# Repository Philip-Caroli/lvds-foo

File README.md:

# lvds-foo
Testing out some LVDS stuff.
Currently only playing around.

## in progress
 * LVDS shield for raspberry (zero) using the DPI interface

## used hardware
 * DPI -> LVDS Converter THC63LVD823B http://www.cel.com/pdf/datasheets/THC63LVD823B.pdf
 * Cable FIX-30P-D6
 * Display HSD150PX17 https://www.touchandscreen.de/mediafiles/Datasheets/HANNSTAR/HSD150PX17-A05.pdf
 
 ## Ressources
  * FIX-30P-D6 and FIX-30P-S8 difference and pinout

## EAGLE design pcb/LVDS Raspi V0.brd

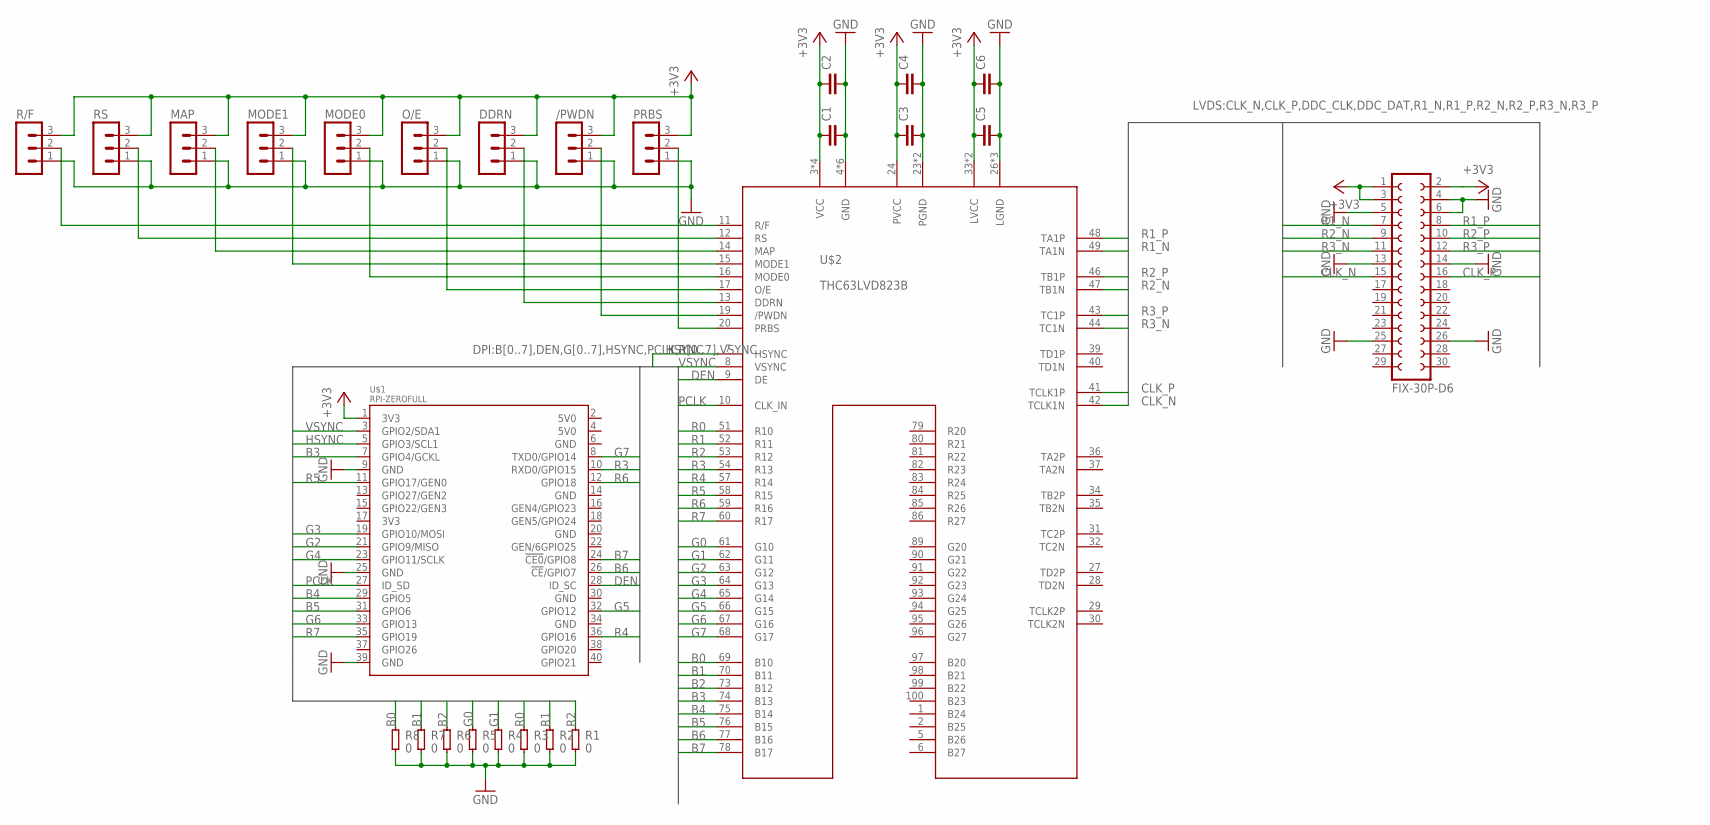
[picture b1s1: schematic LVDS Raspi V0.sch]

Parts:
/PWDN: MA03-1
C1, C2, C3, C4, C5, C6: C0603
DDRN: MA03-1
FIX-30P-D6: FE15-2
MAP: MA03-1
MODE0, MODE1: MA03-1
O/E: MA03-1
PRBS: MA03-1
R1, R2, R3, R4, R5, R6, R7, R8: 0; R0603
R/F: MA03-1
RS: MA03-1
U$1: RPI-ZEROFULL; RASP_PI_ZERO_BOARD_FULL
U$2: THC63LVD823B; QFP50P1600X1600X120-100

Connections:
+3V3: /PWDN.3, C1.1, C2.1, C3.1, C4.1, C5.1, C6.1, DDRN.3, FIX-30P-D6.1, FIX-30P-D6.2, FIX-30P-D6.3, MAP.3, MODE0.3, MODE1.3, O/E.3, PRBS.3, R/F.3, RS.3, U$1.1 (3V3), U$2.3 (VCC), U$2.24 (PVCC), U$2.33 (LVCC), U$2.45 (LVCC), U$2.55 (VCC), U$2.71 (VCC), U$2.87 (VCC)
B0: R8.2, U$2.69 (B10)
B1: R7.2, U$2.70 (B11)
B2: R6.2, U$2.73 (B12)
B3: U$1.7 (GPIO4/GCKL), U$2.74 (B13)
B4: U$1.29 (GPIO5), U$2.75 (B14)
B5: U$1.31 (GPIO6), U$2.76 (B15)
B6: U$1.26 (!CE!/GPIO7), U$2.77 (B16)
B7: U$1.24 (!CE0!/GPIO8), U$2.78 (B17)
CLK_N: FIX-30P-D6.15, U$2.42 (TCLK1N)
CLK_P: FIX-30P-D6.16, U$2.41 (TCLK1P)
DEN: U$1.28 (ID_SC), U$2.9 (DE)
G0: R5.2, U$2.61 (G10)
G1: R4.2, U$2.62 (G11)
G2: U$1.21 (GPIO9/MISO), U$2.63 (G12)
G3: U$1.19 (GPIO10/MOSI), U$2.64 (G13)
G4: U$1.23 (GPIO11/SCLK), U$2.65 (G14)
G5: U$1.32 (GPIO12), U$2.66 (G15)
G6: U$1.33 (GPIO13), U$2.67 (G16)
G7: U$1.8 (TXD0/GPIO14), U$2.68 (G17)
GND: /PWDN.1, C1.2, C2.2, C3.2, C4.2, C5.2, C6.2, DDRN.1, FIX-30P-D6.4, FIX-30P-D6.5, FIX-30P-D6.6, FIX-30P-D6.13, FIX-30P-D6.14, FIX-30P-D6.25, FIX-30P-D6.26, MAP.1, MODE0.1, MODE1.1, O/E.1, PRBS.1, R1.1, R2.1, R3.1, R4.1, R5.1, R6.1, R7.1, R8.1, R/F.1, RS.1, U$1.9 (GND), U$1.25 (GND), U$1.39 (GND), U$2.4 (GND), U$2.18 (GND), U$2.21 (GND), U$2.23 (PGND), U$2.25 (PGND), U$2.26 (LGND), U$2.38 (LGND), U$2.50 (LGND), U$2.56 (GND), U$2.72 (GND), U$2.88 (GND)
HSYNC: U$1.5 (GPIO3/SCL1), U$2.7 (HSYNC)
unnamed: R/F.2, U$2.11 (R/F)
unnamed: RS.2, U$2.12 (RS)
unnamed: MAP.2, U$2.14 (MAP)
unnamed: MODE1.2, U$2.15 (MODE1)
unnamed: MODE0.2, U$2.16 (MODE0)
unnamed: O/E.2, U$2.17 (O/E)
unnamed: DDRN.2, U$2.13 (DDRN)
unnamed: /PWDN.2, U$2.19 (/PWDN)
unnamed: PRBS.2, U$2.20 (PRBS)
PCLK: U$1.27 (ID_SD), U$2.10 (CLK_IN)
R0: R3.2, U$2.51 (R10)
R1: R2.2, U$2.52 (R11)
R1_N: FIX-30P-D6.7, U$2.49 (TA1N)
R1_P: FIX-30P-D6.8, U$2.48 (TA1P)
R2: R1.2, U$2.53 (R12)
R2_N: FIX-30P-D6.9, U$2.47 (TB1N)
R2_P: FIX-30P-D6.10, U$2.46 (TB1P)
R3: U$1.10 (RXD0/GPIO15), U$2.54 (R13)
R3_N: FIX-30P-D6.11, U$2.44 (TC1N)
R3_P: FIX-30P-D6.12, U$2.43 (TC1P)
R4: U$1.36 (GPIO16), U$2.57 (R14)
R5: U$1.11 (GPIO17/GEN0), U$2.58 (R15)
R6: U$1.12 (GPIO18), U$2.59 (R16)
R7: U$1.35 (GPIO19), U$2.60 (R17)
VSYNC: U$1.3 (GPIO2/SDA1), U$2.8 (VSYNC)

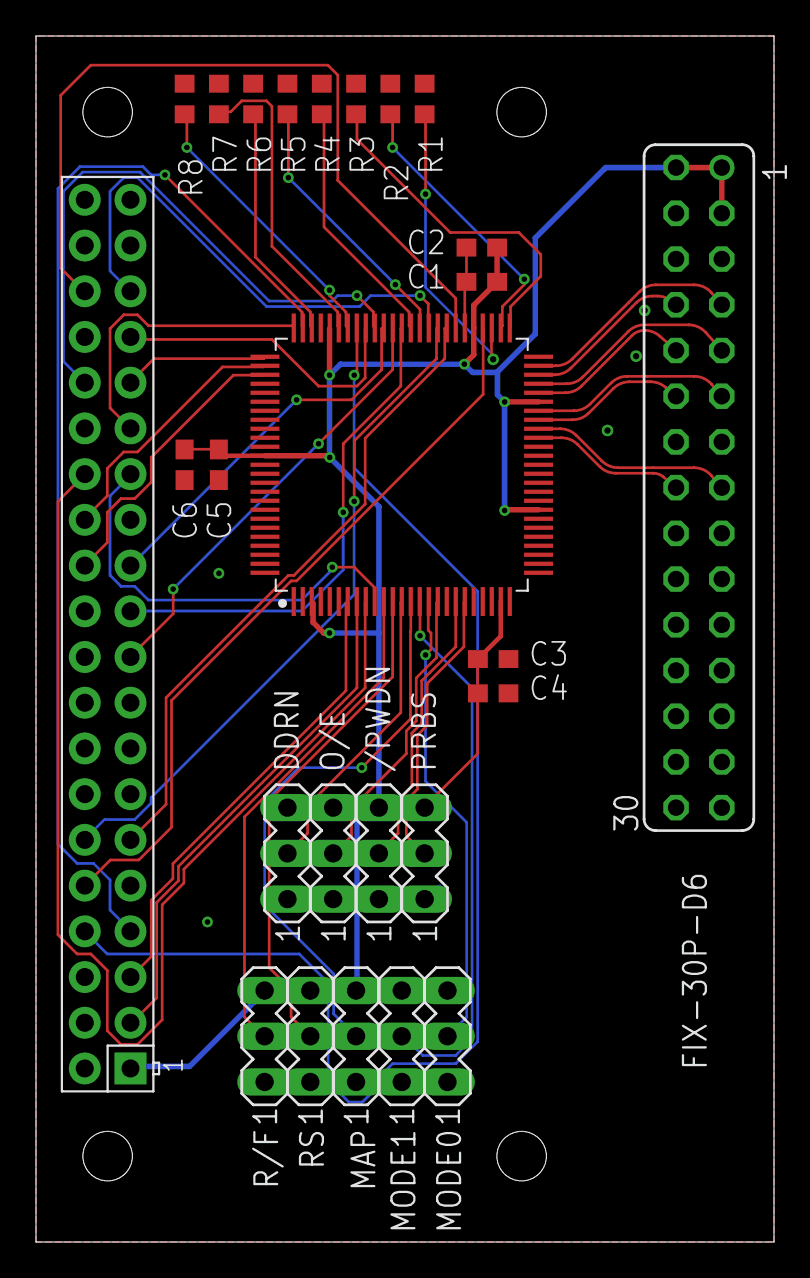
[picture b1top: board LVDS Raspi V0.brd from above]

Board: 2 copper layers, 41.0 x 67.0 mm, 26 parts (0 on the bottom side), 47 nets.

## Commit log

2018-09-28 rounder lines are better lines
